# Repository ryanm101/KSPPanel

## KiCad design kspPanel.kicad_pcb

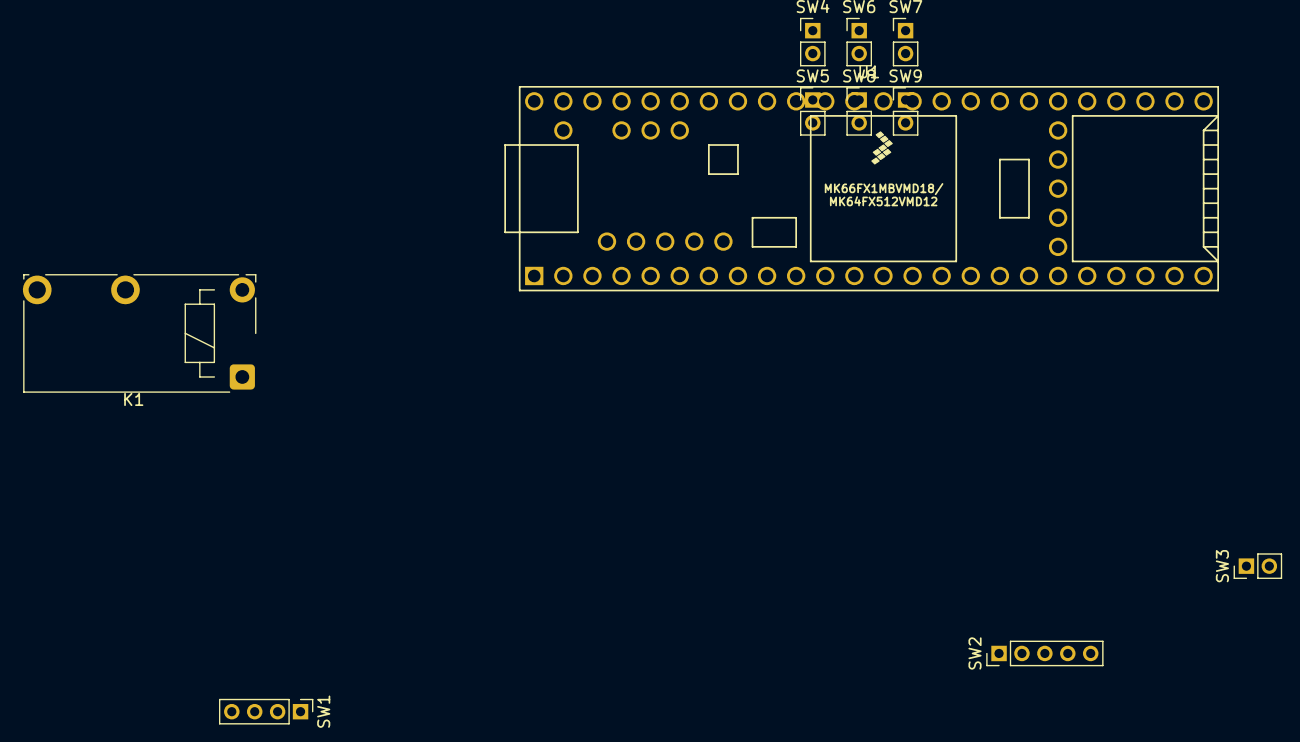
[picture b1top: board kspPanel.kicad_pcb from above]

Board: 2 copper layers, 11 parts (0 on the bottom side), 12 nets, no tracks yet.

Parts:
K1: TE_PCH-1xxx2M; Relay_SPST_TE_PCH-1xxx2M
SW1: SW_DPST; PinHeader_1x04_P2.00mm_Vertical
SW2: SW_Coded_SH-7010; PinHeader_1x05_P2.00mm_Vertical
SW3, SW4, SW6, SW7, SW8: SW_SPST; PinHeader_1x02_P2.00mm_Vertical
SW5, SW9: SW_Push; PinHeader_1x02_P2.00mm_Vertical
U1: Teensy3.5; Teensy35_36

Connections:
/3.3v_PWR: SW1.2, SW5.1, SW9.1, U1.16
/5v_PWR: K1.3, SW3.1, SW4.1, SW6.1, SW7.1, SW8.1
/ABORT: SW5.2, U1.22
/RCS_TOGGLE: SW3.2, U1.21
/SAS_P1: SW2.1, U1.17
/SAS_P2: SW2.2, U1.18
/SAS_P4: SW2.4, U1.19
/SAS_SELECT: SW9.2, U1.13
/SAS_TOGGLE: SW6.2, U1.14
/U1_3.3v: SW1.1, SW1.3, U1.15
GND: K1.5, U1.1
unnamed: K1.1, SW1.4

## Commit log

2019-10-25 Added some datasheets
2019-10-29 Added datasheet for rotary switch
